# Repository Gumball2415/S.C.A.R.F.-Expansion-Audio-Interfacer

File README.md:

# S.C.A.R.F. Expansion Audio Interfacer

An Open-Source HardWare (OSHW) Famicom expansion audio interfacer.

Currently a work in progress, completed but untested!!!
28/FEB/2023: this repo is now archived, i may have to start from scratch with what i learned since i started this.

## PCB Specifications

Note that this project is optimized for JLCPCB manufacturing, so you may have to modify the gerber export, remove the "JLCJLCJLCJLC" silkscreen text, etc.
Please use the gerber exports in each release.

### Motherboard

- 2 layers
- 222.64mm x 122.24mm
- 1.6mm thickness
- ENIG-RoHS surface finish recommended
- Any soldermask color you want!

### Cartridge Adapters

- 2 layers
- Multiple footprints in gerber, might need to manually panelize
- 1.2mm thickness
- ENIG-RoHS surface finish recommended; Gold fingers optional
- Beveled edge, chamfer cut
- Any soldermask color you want!

## License

- The PCB and schematics are licensed under the TAPR Open Hardware License ([www.tapr.org/OHL](http://www.tapr.org/OHL)).
- The PLD source code files are licensed under GPL 2.0 or higher. (https://www.gnu.org/licenses/old-licenses/gpl-2.0.html)
- © Persune 2021

## Credits

- lidnariq, grievre, Iyatemu, and plgDavid; thank you for being patient with me and my inquiry!
- Iyatemu - providing custom footprints and schematic symbols
- lidnariq - providing advice for my schematics and addressing logic
- grievre - providing advice for my PCB design
- Special thanks to the NESDEV community, this project wouldn't have been possible without their extensive help!

## Support

Support me on [Ko-Fi](https://ko-fi.com/persune) to help me afford hardware development equipment and further improve this project!

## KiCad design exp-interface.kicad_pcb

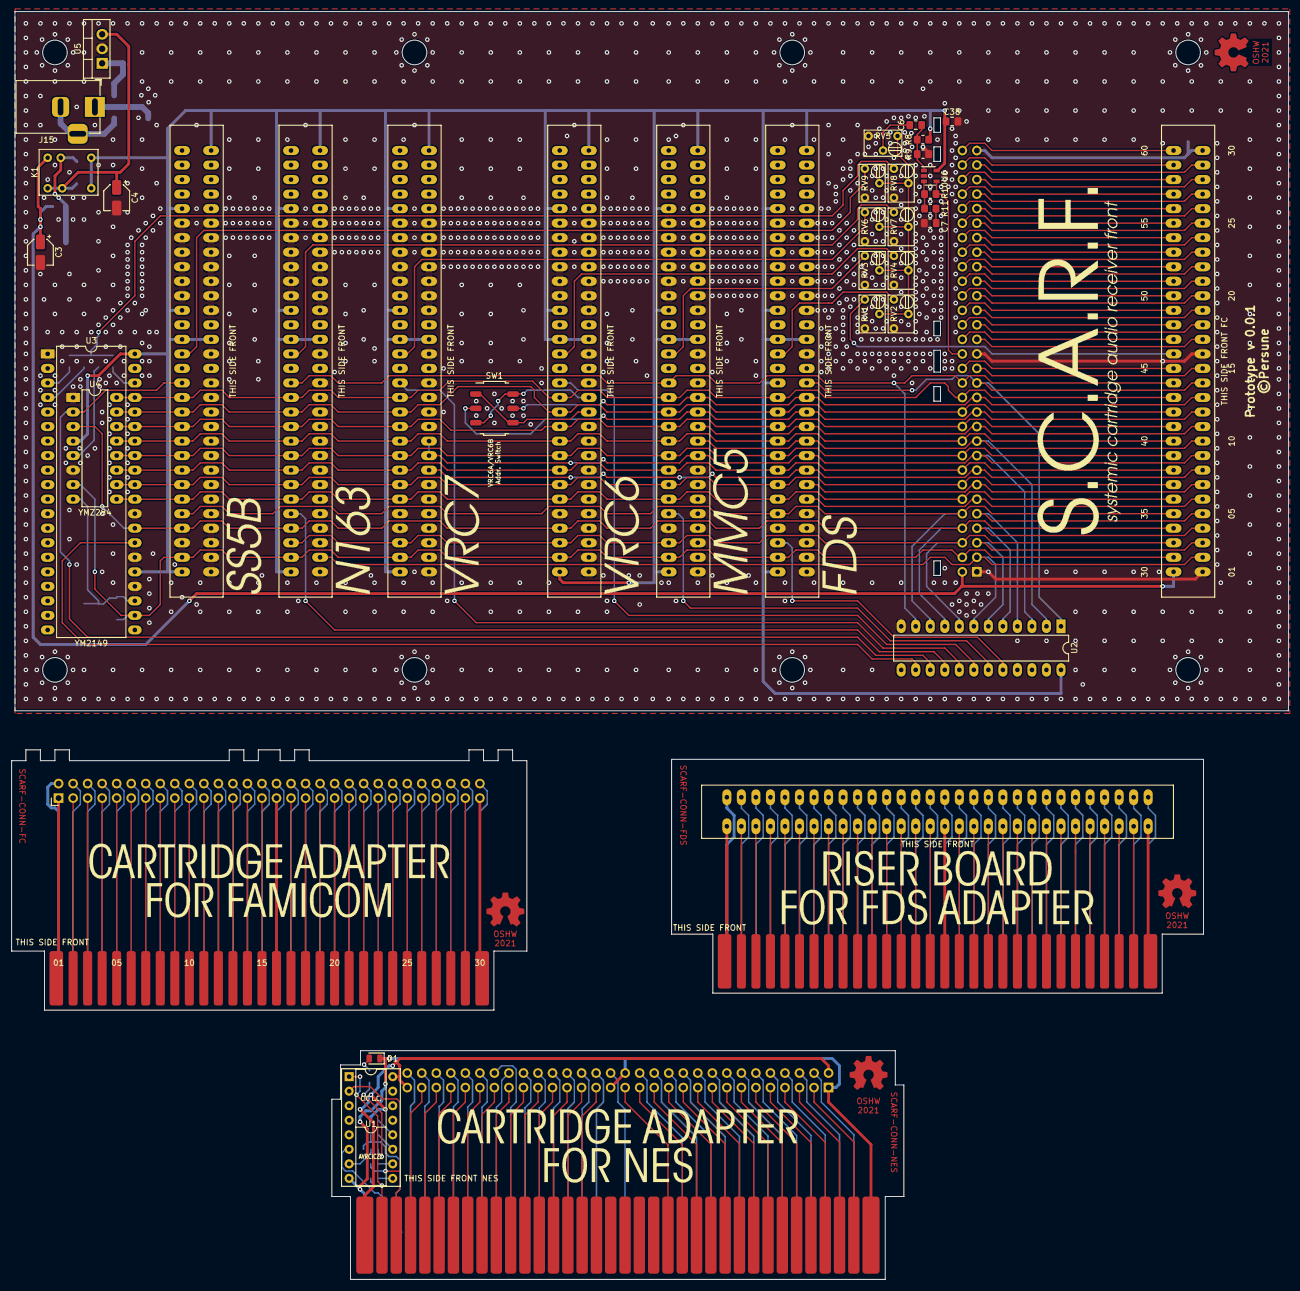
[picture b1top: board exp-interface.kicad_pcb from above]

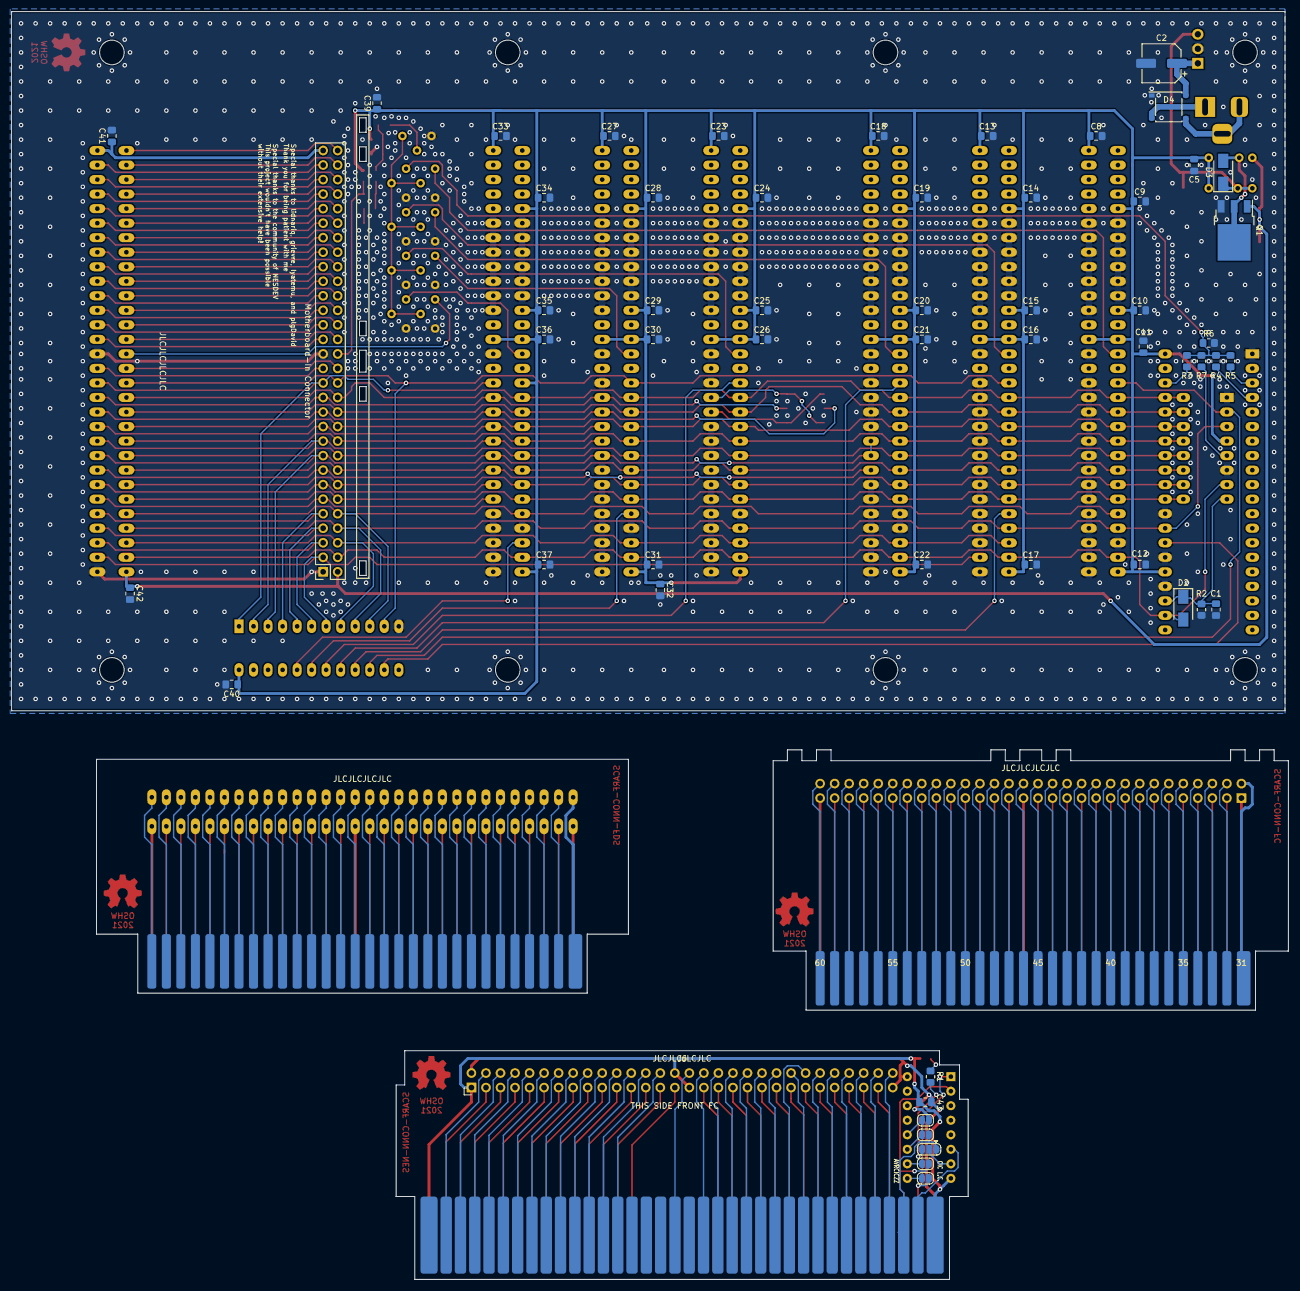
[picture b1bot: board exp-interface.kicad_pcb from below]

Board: 2 copper layers, 222.6 x 122.2 mm, 96 parts (56 on the bottom side), 102 nets.

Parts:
C1: 10pF; C_0805_2012Metric_Pad1.18x1.45mm_HandSolder
C2: 100uF; CP_Elec_6.3x5.8
C3, C4: 10uF; CP_Elec_4x3.9
C5, C8, C9, C10, C11, C12, C13, C14, C15, C16, C17, C18, C19, C20, C21, C22, C23, C24, C25, C26, C27, C28, C29, C30, C31, C32, C33, C34, C35, C36, C37, C38, C39, C40, C41, C42, C43: 100nF; C_0805_2012Metric_Pad1.18x1.45mm_HandSolder
C6, C7: 390nF; C_0805_2012Metric_Pad1.18x1.45mm_HandSolder
D1: SML-H12D8T; LED_0805_2012Metric
D2, D3: 1N4004; D_SMA
D4: ABS210; Diode_Bridge_Diotec_ABS
J1: FamiCom Console Connector; FC_CONN
J2: FC Connector Board Out Connector; PinHeader_2x30_P2.54mm_Horizontal_rewire
J3: Motherboard-In Connector; PinHeader_2x30_P2.54mm_Vertical_rewire
J4: Motherboard Connector; FC_CONN
J5: FDS Connector; FC_CONN_F_FDS
J6: NES Connector Board Out Connector; PinHeader_2x30_P2.54mm_Horizontal_rewire
J7: Host Cart Connector; FC_CONN_F
J8: NES Console Connector; NES-CONN
J9: SS5B Connector; FC_CONN_F
J10: N163 Connector; FC_CONN_F
J11: VRC7 Connector; FC_CONN_F
J12: VRC6 Connector; FC_CONN_F
J13: MMC5 Connector; FC_CONN_F
J14: FDS Riser Connector; FC_CONN_F
J15: Barrel_Jack_Switch; BarrelJack_Horizontal
JP1: SolderJumper_3_Open; SolderJumper-3_P1.3mm_Open_RoundedPad1.0x1.5mm
JP2, JP3, JP4, JP5: SolderJumper_2_Open; SolderJumper-2_P1.3mm_Open_RoundedPad1.0x1.5mm
K1: HRA-S-DC5V
Q1: 2SK2415; TO-252-3_TabPin2
R1: 270; R_0805_2012Metric_Pad1.20x1.40mm_HandSolder
R2, R8, R9: 10K; R_0805_2012Metric_Pad1.20x1.40mm_HandSolder
R3, R4, R5, R7: 1K; R_0805_2012Metric_Pad1.20x1.40mm_HandSolder
R6: 3K; R_0805_2012Metric_Pad1.20x1.40mm_HandSolder
R10: 100K; R_0805_2012Metric_Pad1.20x1.40mm_HandSolder
R11: 20K; R_0805_2012Metric_Pad1.20x1.40mm_HandSolder
RV1, RV2, RV3, RV4, RV5, RV6, RV7, RV8, RV9: 3266W-1-503LF; 3266W
SW1: SS-3235S-L3
U1: CIC_Lockout_Chip; DIP-16_W7.62mm_Socket
U2: ATF22V10C-15PU; DIP-24_W7.62mm_LongPads
U3: YM2149; DIP-40_W15.24mm_LongPads
U4: YMZ284; DIP-16_W7.62mm_LongPads
U5: L78S05; TO-220-3_Vertical
U6: LM321; SOT-23-5

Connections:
AUD_IN: J1.45, J2.45, J3.45, J4.45, J5.45, J7.45
AUD_OUT: J1.46, J2.46, J4.46, J5.46, J6.46, J8.54, R10.1, U6.4
CIC_+RST: J8.70, JP1.1, JP3.2
CIC_CLK: J8.71, U1.6
CIC_TO_MB: J8.35, JP5.2, U1.1
CIC_TO_PAK: J8.34, JP4.2, U1.2
CIRAM_A10: J1.18, J2.18, J3.18, J4.18, J5.18, J6.18, J7.18, J8.22
CIRAM_~CE: J1.48, J2.48, J3.48, J4.48, J5.48, J6.48, J7.48, J8.57
CPU_A0: J1.13, J2.13, J3.13, J4.13, J5.13, J6.13, J7.13, J8.13, J13.13, J14.13, SW1.5
CPU_A1: J1.12, J2.12, J3.12, J4.12, J5.12, J6.12, J7.12, J8.12, J13.12, J14.12, SW1.2
CPU_A2: J1.11, J2.11, J3.11, J4.11, J5.11, J6.11, J7.11, J8.11, J13.11, J14.11
CPU_A3: J1.10, J2.10, J3.10, J4.10, J5.10, J6.10, J7.10, J8.10, J13.10, J14.10, U2.2
CPU_A4: J1.9, J2.9, J3.9, J4.9, J5.9, J6.9, J7.9, J8.9, J11.9, J11.10, J13.9, J14.9, U2.3
CPU_A5: J1.8, J2.8, J3.8, J4.8, J5.8, J6.8, J7.8, J8.8, J11.8, J14.8
CPU_A6: J1.7, J2.7, J3.7, J4.7, J5.7, J6.7, J7.7, J8.7, J14.7
CPU_A7: J1.6, J2.6, J3.6, J4.6, J5.6, J6.6, J7.6, J8.6, J14.6
CPU_A8: J1.5, J2.5, J3.5, J4.5, J5.5, J6.5, J7.5, J8.5, U2.4
CPU_A9: J1.4, J2.4, J3.4, J4.4, J5.4, J6.4, J7.4, J8.4, U2.5
CPU_A10: J1.3, J2.3, J3.3, J4.3, J5.3, J6.3, J7.3, J8.3, U2.6
CPU_A11: J1.2, J2.2, J3.2, J4.2, J5.2, J6.2, J7.2, J8.2, J10.2, U2.7
CPU_A12: J1.33, J2.33, J3.33, J4.33, J5.33, J6.33, J7.33, J8.39, J10.33, J11.33, J12.33, J13.33, U2.8
CPU_A13: J1.34, J2.34, J3.34, J4.34, J5.34, J6.34, J7.34, J8.40, J9.34, J10.34, J12.34, U2.9, U3.28, U4.3
CPU_A14: J1.35, J2.35, J3.35, J4.35, J5.35, J6.35, J7.35, J8.41, J9.35, J14.35, U2.10
CPU_D0: J1.43, J2.43, J3.43, J4.43, J5.43, J6.43, J7.43, J8.49, J9.43, J10.43, J11.43, J12.43, J13.43, J14.43, U3.37, U4.16
CPU_D1: J1.42, J2.42, J3.42, J4.42, J5.42, J6.42, J7.42, J8.48, J9.42, J10.42, J11.42, J12.42, J13.42, J14.42, U3.36, U4.15
CPU_D2: J1.41, J2.41, J3.41, J4.41, J5.41, J6.41, J7.41, J8.47, J9.41, J10.41, J11.41, J12.41, J13.41, J14.41, U3.35, U4.14
CPU_D3: J1.40, J2.40, J3.40, J4.40, J5.40, J6.40, J7.40, J8.46, J9.40, J10.40, J11.40, J12.40, J13.40, J14.40, U3.34, U4.13
CPU_D4: J1.39, J2.39, J3.39, J4.39, J5.39, J6.39, J7.39, J8.45, J9.39, J10.39, J11.39, J12.39, J13.39, J14.39, U3.33, U4.12
CPU_D5: J1.38, J2.38, J3.38, J4.38, J5.38, J6.38, J7.38, J8.44, J9.38, J10.38, J11.38, J12.38, J13.38, J14.38, U3.32, U4.11
CPU_D6: J1.37, J2.37, J3.37, J4.37, J5.37, J6.37, J7.37, J8.43, J9.37, J10.37, J11.37, J12.37, J13.37, J14.37, U3.31, U4.10
CPU_D7: J1.36, J2.36, J3.36, J4.36, J5.36, J6.36, J7.36, J8.42, J9.36, J10.36, J11.36, J12.36, J13.36, J14.36, U3.30, U4.9
CPU_R~W: J1.14, J2.14, J3.14, J4.14, J5.14, J6.14, J7.14, J8.14, J14.14, U2.1
FDS_AUD_OUT: J14.46, RV2.1
FDS_ENABLE: J14.33, U2.20
GND: C1.2, C2.2, C3.2, C4.2, C5.2, C7.2, C8.2, C9.2, C10.2, C11.2, C12.2, C13.2, C14.2, C15.2, C16.2, C17.2, C18.2, C19.2, C20.2, C21.2, C22.2, C23.2, C24.2, C25.2, C26.2, C27.2, C28.2, C29.2, C30.2, C31.2, C32.2, C33.2, C34.2, C35.2, C36.2, C37.2, C38.2, C39.2, C40.2, C41.2, C42.2, C43.2, D1.1, D4.1, J1.1, J1.16, J2.1, J2.16, J3.1, J3.16, J4.1, J4.16, J5.1, J5.16, J6.1, J6.16, J6.45, J7.1, J7.16, J8.1, J8.72, J9.1, J9.2, J9.3, J9.4, J9.5, J9.6, J9.7, J9.8, J9.9, J9.10, J9.11, J9.12, J9.13, J9.14, J9.16, J9.19, J9.20, J9.21, J9.22, J9.23, J9.24, J9.25, J9.33, J9.50, J9.51, J9.52, J9.53, J9.54, J9.55, J10.1, J10.3, J10.4, J10.5, J10.6, J10.7, J10.8, J10.9, J10.10, J10.11, J10.12, J10.13, J10.14, J10.16, J10.19, J10.20, J10.21, J10.22, J10.23, J10.24, J10.25, J10.50, J10.51, J10.52, J10.53, J10.54, J10.55, J11.1, J11.2, J11.3, J11.4, J11.5, J11.6, J11.7, J11.11, J11.12, J11.13, J11.14, J11.16, J11.19, J11.20, J11.21, J11.22, J11.23, J11.24, J11.25, J11.34, J11.35, J11.50, J11.51, J11.52, J11.53, J11.54, J11.55, J12.1, J12.2, J12.3, J12.4, J12.5, J12.6, J12.7, J12.8, J12.9, J12.10, J12.11, J12.14, J12.16, J12.19, J12.20, J12.21, J12.22, J12.23, J12.24, J12.25, J12.35, J12.50, J12.51, J12.52, J12.53, J12.54, J12.55, J13.1, J13.2, J13.3, J13.4, J13.5, J13.6, J13.7, J13.8, J13.14, J13.16, J13.19, J13.20, J13.21, J13.22, J13.23, J13.24, J13.25, J13.34, J13.50, J13.51, J13.52, J13.53, J13.54, J13.55, J14.1, J14.2, J14.3, J14.4, J14.5, J14.16, J14.19, J14.20, J14.21, J14.22, J14.23, J14.24, J14.25, J14.34, J14.50, J14.51, J14.52, J14.53, J14.54, J14.55, Q1.3, R2.2, R6.2, R9.1, RV1.3, RV2.3, RV3.3, RV4.3, RV5.3, RV6.3, RV7.3, RV8.3, RV9.3, U1.8, U2.12, U3.1, U3.24, U3.26, U3.29, U4.1, U4.6, U5.2, U6.2
HOST_AUD_OUT: J3.46, J7.46, RV1.1
M2: D2.2, J1.32, J2.32, J3.32, J4.32, J5.32, J6.32, J7.32, J8.38, J9.32, J10.32, J11.32, J12.32, J13.32, J14.32, U3.22, U4.7
MMC5_AUD_OUT: J13.46, RV3.1
MMC5_ENABLE: J13.35, U2.19
N163_AUD_OUT: J10.46, RV7.1
N163_ENABLE: J10.35, U2.16
unnamed: C2.1, D4.4, U5.1
unnamed: C4.1, D3.1, K1.2, K1.3, U5.3
unnamed: C6.1, RV5.2
unnamed: C6.2, R8.1, R9.2, U6.1
unnamed: C7.1, R11.2
unnamed: D1.2, R1.1
unnamed: D3.2, K1.5, Q1.2
unnamed: D4.2, J15.1
unnamed: D4.3, J15.2, J15.3
unnamed: J12.12, SW1.1, SW1.6
unnamed: J12.13, SW1.3, SW1.4
unnamed: JP1.2, U1.7
unnamed: JP1.3, R1.2
unnamed: JP2.1, U1.12
unnamed: JP3.1, U1.11
unnamed: JP4.1, U1.10
unnamed: JP5.1, U1.9
unnamed: R3.2, U3.38
unnamed: R4.2, U3.4
unnamed: R5.2, U3.3
unnamed: R7.1, U4.5
unnamed: R10.2, R11.1, U6.3
unnamed: RV1.2, RV2.2, RV3.2, RV4.2, RV5.1, RV6.2, RV7.2, RV8.2, RV9.2
PPU_A0: J1.25, J2.25, J3.25, J4.25, J5.25, J6.25, J7.25, J8.29
PPU_A1: J1.24, J2.24, J3.24, J4.24, J5.24, J6.24, J7.24, J8.28
PPU_A2: J1.23, J2.23, J3.23, J4.23, J5.23, J6.23, J7.23, J8.27
PPU_A3: J1.22, J2.22, J3.22, J4.22, J5.22, J6.22, J7.22, J8.26
PPU_A4: J1.21, J2.21, J3.21, J4.21, J5.21, J6.21, J7.21, J8.25
PPU_A5: J1.20, J2.20, J3.20, J4.20, J5.20, J6.20, J7.20, J8.24
PPU_A6: J1.19, J2.19, J3.19, J4.19, J5.19, J6.19, J7.19, J8.23
PPU_A7: J1.50, J2.50, J3.50, J4.50, J5.50, J6.50, J7.50, J8.59
PPU_A8: J1.51, J2.51, J3.51, J4.51, J5.51, J6.51, J7.51, J8.60
PPU_A9: J1.52, J2.52, J3.52, J4.52, J5.52, J6.52, J7.52, J8.61
PPU_A10: J1.53, J2.53, J3.53, J4.53, J5.53, J6.53, J7.53, J8.63
PPU_A11: J1.54, J2.54, J3.54, J4.54, J5.54, J6.54, J7.54, J8.62
PPU_A12: J1.55, J2.55, J3.55, J4.55, J5.55, J6.55, J7.55, J8.64
PPU_A13: J1.56, J2.56, J3.56, J4.56, J5.56, J6.56, J7.56, J8.65
PPU_D0: J1.26, J2.26, J3.26, J4.26, J5.26, J6.26, J7.26, J8.30
PPU_D1: J1.27, J2.27, J3.27, J4.27, J5.27, J6.27, J7.27, J8.31
PPU_D2: J1.28, J2.28, J3.28, J4.28, J5.28, J6.28, J7.28, J8.32
PPU_D3: J1.29, J2.29, J3.29, J4.29, J5.29, J6.29, J7.29, J8.33
PPU_D4: J1.60, J2.60, J3.60, J4.60, J5.60, J6.60, J7.60, J8.69
PPU_D5: J1.59, J2.59, J3.59, J4.59, J5.59, J6.59, J7.59, J8.68
PPU_D6: J1.58, J2.58, J3.58, J4.58, J5.58, J6.58, J7.58, J8.67
PPU_D7: J1.57, J2.57, J3.57, J4.57, J5.57, J6.57, J7.57, J8.66
PPU_~A13: J1.49, J2.49, J3.49, J4.49, J5.49, J6.49, J7.49, J8.58
PPU_~RD: J1.17, J2.17, J3.17, J4.17, J5.17, J6.17, J7.17, J8.21
PPU_~WR: J1.47, J2.47, J3.47, J4.47, J5.47, J6.47, J7.47, J8.56
S5B_AUD_OUT: J9.46, RV8.1
S5B_ENABLE: J9.44, U2.15, U4.2
SSG_AUD_OUT: R3.1, R4.1, R5.1, R6.1, R7.2, RV9.1
SSG_CE: U2.14, U3.27
SSG_~RESET: C1.1, D2.1, R2.1, U3.23, U4.8
VCC: C5.1, C8.1, C9.1, C10.1, C11.1, C12.1, C13.1, C14.1, C15.1, C16.1, C17.1, C18.1, C19.1, C20.1, C21.1, C22.1, C23.1, C24.1, C25.1, C26.1, C27.1, C28.1, C29.1, C30.1, C31.1, C32.1, C33.1, C34.1, C35.1, C36.1, C37.1, C38.1, C39.1, C40.1, J4.30, J4.31, J5.30, J5.31, J9.17, J9.30, J9.31, J9.47, J9.49, J9.56, J10.17, J10.30, J10.31, J10.47, J10.49, J10.56, J11.17, J11.30, J11.31, J11.47, J11.49, J11.56, J12.17, J12.30, J12.31, J12.47, J12.49, J12.56, J13.17, J13.30, J13.31, J13.47, J13.49, J13.56, J14.17, J14.30, J14.31, J14.44, J14.47, J14.49, J14.56, K1.1, K1.6, R8.2, U2.24, U3.25, U3.40, U4.4, U6.5
VCC_CART: C3.1, C41.1, C42.1, C43.1, J1.30, J1.31, J2.30, J2.31, J3.30, J3.31, J6.30, J6.31, J7.30, J7.31, J8.36, JP2.2, K1.4, Q1.1, U1.16
VRC6_AUD_OUT: J12.46, RV4.1
VRC6_ENABLE: J12.44, U2.18
VRC7_AUD_OUT: J11.46, RV6.1
VRC7_ENABLE: J11.44, U2.17
~IRQ: J1.15, J2.15, J3.15, J4.15, J5.15, J6.15, J7.15, J8.15
~ROMSEL: J1.44, J2.44, J3.44, J4.44, J5.44, J6.44, J7.44, J8.50, J10.44, J13.44, U2.11

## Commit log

2021-11-18 Version 0.0.1
2021-12-08 Add PCB specifications
2021-12-08 Add board dimensions
